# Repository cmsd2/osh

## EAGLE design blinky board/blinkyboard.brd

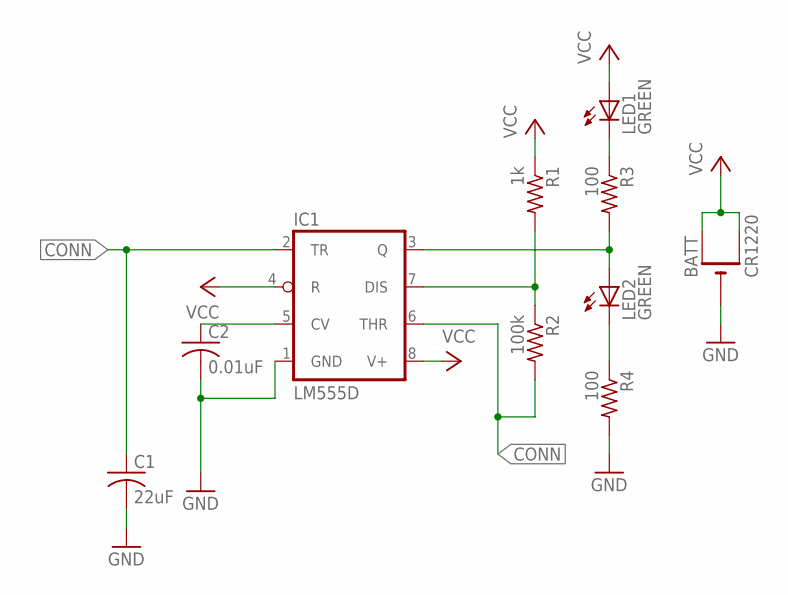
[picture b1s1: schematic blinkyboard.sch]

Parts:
BATT: CR1220; CR1220-SMD; MPN 3001
C1: 22uF; C0805; MPN C0805C226M9PACTU
C2: 0.01uF; C0805; MPN 04023D103KAT2A
IC1: LM555D; SO08; MPN TLC555CDR
LED1, LED2: GREEN; CHIPLED_0805; MPN 5988170107F
R1: 1k; R0805; MPN CRCW08051K00FKEA
R2: 100k; R0805; MPN CRCW0805100KFKEA
R3, R4: 100; R0805; MPN CR0805-JW-101ELF

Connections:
CONN: C1.1, IC1.2 (TR), IC1.6 (THR), R2.2
GND: BATT.-, C1.2, C2.2, IC1.1 (GND), R4.2
unnamed: LED1.C, R3.1
unnamed: IC1.3 (Q), LED2.A, R3.2
unnamed: LED2.C, R4.1
unnamed: IC1.7 (DIS), R1.2, R2.1
unnamed: C2.1, IC1.5 (CV)
VCC: BATT.+$1 (+), BATT.+$2 (+1), IC1.4 (R), IC1.8 (V+), LED1.A, R1.1

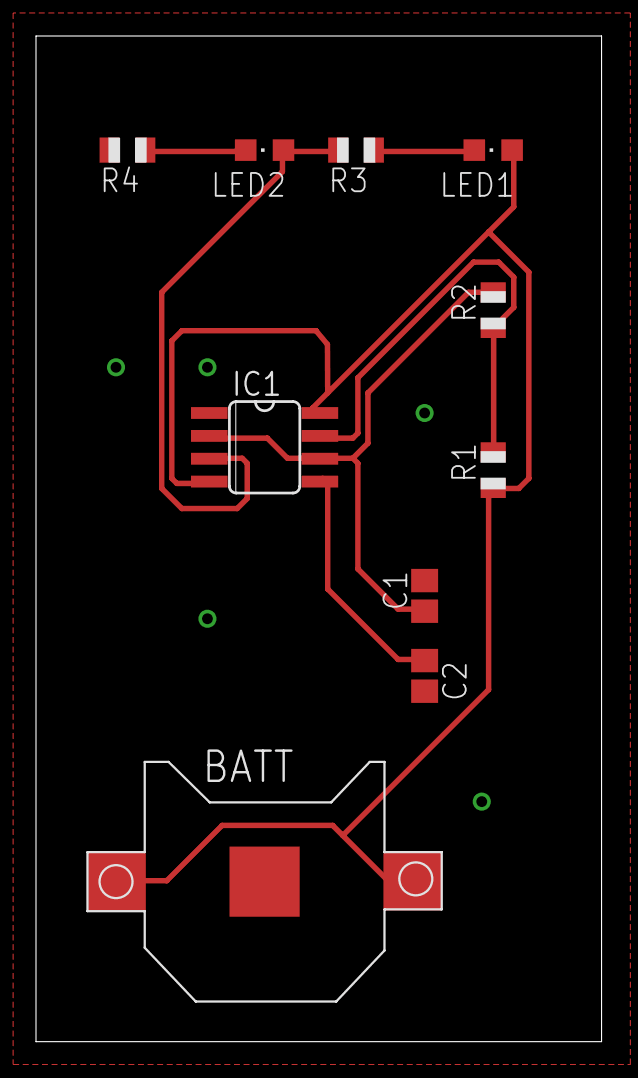
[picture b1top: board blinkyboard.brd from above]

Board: 2 copper layers, 31.4 x 55.9 mm, 10 parts (0 on the bottom side), 8 nets.

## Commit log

2015-04-22 basic blinkyboard from jeremy blum's eagle tutorial
2015-04-22 code from jeremy's tutorial is GPLv3
2015-05-13 lpc810 blinky
2015-05-13 reverse polarity protection using a p-channel mosfet
2015-05-13 add readme
2015-05-13 add link
2024-08-08 simple led torch schematic
2024-08-09 add components to pcb
2024-08-10 basic layout
2024-08-10 complete layout
2024-08-10 add battery charging circuit
2024-08-15 reference design for battery charger
2024-08-30 add led strip driver reference
2024-09-02 complete pcb for led driver
2024-09-02 flip pwm connector so gnd pad is square
2025-08-29 add buck boost test
2025-09-22 add 555 astable timer
2025-09-22 add spreadsheet for calculating resistor values
2025-10-02 add pcb design and lcsc part numbers
2025-10-07 add atf1504asv breakout board
2025-10-09 route tracks and add graphics
2025-10-10 add power-on-reset and switch and led peripherals
2025-10-11 replace two of the mounting holes with tooling holes for assembly
2025-10-16 add 3.3v buck power test circuit
2025-10-16 tidy up
2025-10-16 add graphics
2025-10-16 update part numbers
2025-10-16 ignore
